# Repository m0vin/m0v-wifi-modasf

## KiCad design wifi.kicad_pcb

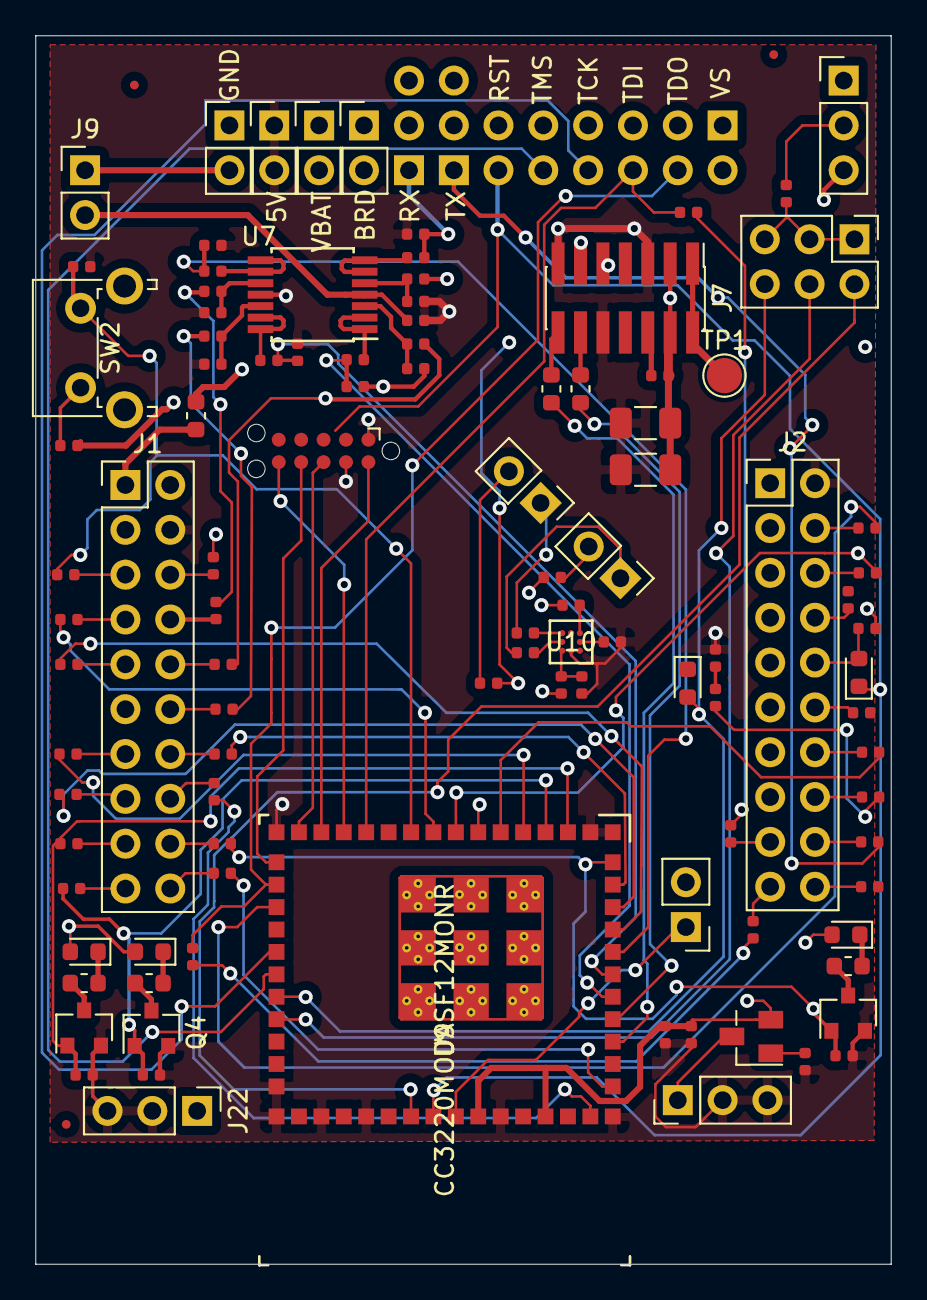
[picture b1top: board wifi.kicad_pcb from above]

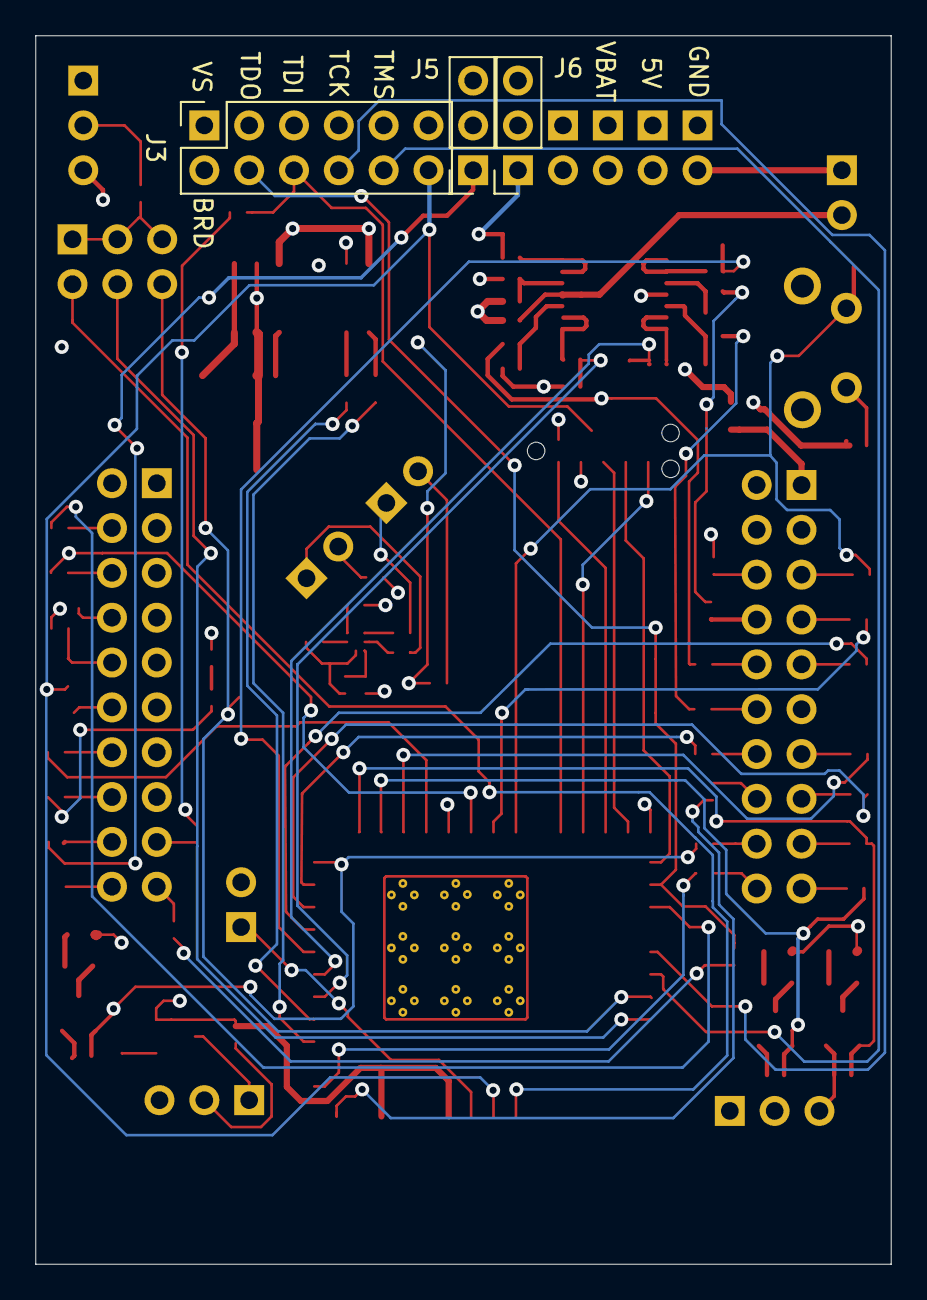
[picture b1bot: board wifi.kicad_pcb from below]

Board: 4 copper layers, 48.5 x 69.6 mm, 109 parts (3 on the bottom side), 107 nets.

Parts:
C26, C27, C28, C29, C30: 0.01uF; C_0402_1005Metric
C33, C34, C35: 0.1uF; C_0402_1005Metric
C41, C42: 100uF; C_1206_3216Metric
D4, D5: D_Schottky; D_0603_1608Metric
D8, D9, D10: LED; LED_0603_1608Metric
FID1, FID2, FID3: Fiducial; Fiducial_0.5mm_Mask1mm
J1, J2: Conn_02x10_Odd_Even; PinHeader_2x10_P2.54mm_Vertical
J3: Conn_02x06_Odd_Even; PinSocket_2x06_P2.54mm_Vertical
J5, J6: Conn_01x03; PinSocket_1x03_P2.54mm_Vertical
J7: Conn_02x07_Odd_Even; PinHeader_2x07_P1.27mm_Vertical_SMD
J9, J10, J14, J15, J16, J18, J19, J20: Conn_01x02; PinHeader_1x02_P2.54mm_Vertical
J12: Conn_02x03_Odd_Even; PinHeader_2x03_P2.54mm_Vertical
J13: Conn_02x05_Counter_Clockwise; Tag-Connect_TC2050-IDC-NL_2x05_P1.27mm_Vertical_CC_SMD
J21, J22, J26: Conn_01x03; PinHeader_1x03_P2.54mm_Vertical
Q4, Q6, Q7: BSS138; SOT-23
Q5: TP0610T; SuperSOT-3
R31, R136: 1K; R_0402_1005Metric
R33, R34: 33; R_0603_1608Metric
R38: 0; R_0603_1608Metric
R42, R44, R46, R49, R50, R52, R53, R54, R56, R57, R58, R60, R62, R63, R64, R65, R66, R67, R68, R69, R70, R71, R72, R73, R74, R104, R105, R114, R119, R121, R126, R127, R132, R133, R152: 0; R_0402_1005Metric
R84, R87, R92, R93: 470; R_0402_1005Metric
R85, R86, R94, R95: 576K; R_0402_1005Metric
R88, R89, R96, R97: 422K; R_0402_1005Metric
R107: 270; R_0402_1005Metric
R109: 2.2K; R_0402_1005Metric
R113, R139: 10K; R_0402_1005Metric
R134, R149, R150, R151: 100K; R_0402_1005Metric
R145, R146, R147: 270; R_0603_1608Metric
SW2: SW_DIP_x01; SW_Tactile_SPST_Angled_PTS645Vx31-2LFS
TP1: TestPoint; TestPoint_Pad_D2.0mm
U7: OPA4340UA; TSSOP-14_4.4x5mm_P0.65mm
U9: CC3220MODASF12MONR
U10: TMP006AIYZFR

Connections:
/ANA_IN1: R50.2, R86.2
/ANA_IN2: R58.2, R94.2
/ANA_IN3: R62.2, R95.2
/ANA_IN4: R54.2, R85.1
/CC_nRESET: D5.1, J3.12, J13.2, U9.35
/GPIO: J1.9, R57.1
/LP_GPIO_01: J5.1, R64.1
/LP_GPIO_02: C28.2, J6.1, R87.2
/LP_RESET_OUT: D5.2, J2.10, R134.2
/P01_GPIO_10: J7.9, Q6.1, R71.2, R121.2, R150.1, U9.3
/P02_GPIO_11: J7.11, Q4.1, R73.2, R127.2, R149.1, U9.4
/P03_GPIO_12: R53.2, U9.9
/P04_GPIO_13: R49.2, R139.1, SW2.2, U9.10
/P05_GPIO_14: R65.2, U9.5
/P06_GPIO_15: R56.1, U9.6
/P08_GPIO_17: R44.1, U9.8
/P16_GPIO_23: R63.2, R105.2
/P16_JTAG_TDI: J3.6, R105.1, U9.12
/P17_GPIO_24: R67.2, R104.2
/P17_JTAG_TDO: J3.4, R104.1, U9.18
/P18_GPIO_28: R42.1, U9.19
/P19_JTAG_TCK: J3.8, U9.21
/P20_JTAG_TMS: J3.10, U9.22
/P21_GPIO_25: R60.1, R109.1
/P50_GPIO_00: R74.2, U9.44
/P53_GPIO_30: R70.2, U9.42
/P55_GPIO_01: J5.2, R34.1, U9.46
/P57_GPIO_02: J6.2, R33.1, U9.47
/P58_GPIO_03: C29.2, R92.2, U9.48
/P59_GPIO_04: C30.2, R93.2, U9.49
/P60_GPIO_05: C27.2, R84.2, U9.50
/P61_GPIO_06: R57.2, U9.51
/P62_GPIO_07: R69.2, U9.52
/P63_GPIO_08: R66.2, U9.53
/P64_GPIO_09: Q7.1, R72.2, R151.1, U9.54
/PWR: J1.1, R38.1
/RX: J1.5, R49.1
/SENS_I2C_SCL: J14.1, R132.2
/SENS_I2C_SDA: J15.1, R133.1
/SOP0: J12.2, U9.34
/SOP1: J12.4, U9.24
/SOP2: D4.2, J12.6, U9.23
/SPI_CLK: J13.8, U9.15
/SPI_CS_IN: J13.10, U9.14
/SPI_MISO: J13.6, U9.13
/SPI_MOSI: J13.7, U9.17
/TX: J1.7, R53.1
/VBAT_CC: C33.1, C34.1, C41.2, C42.2, J7.3, J7.4, J10.2, J18.2, J26.3, Q5.2, R31.2, R38.2, U9.37, U9.40
/VCC_5V: J1.2, J19.2, J22.1
/VCC_BRD: D8.2, D9.2, D10.2, J3.2, J9.1, J16.2, J26.1, R114.1, R119.2, R134.1, R136.1
/VCC_LDO_3V3: J16.1, J18.1
/VCC_OPAMP: C26.2, J9.2, U7.4
GND: C26.1, C27.1, C28.1, C29.1, C30.1, C33.2, C34.2, C35.1, C41.1, C42.1, J1.4, J2.2, J7.5, J7.10, J7.13, J13.1, J13.9, J20.1, J20.2, J21.2, J21.3, J22.2, J22.3, Q4.2, Q6.2, Q7.2, R88.1, R89.1, R96.1, R97.1, R113.1, R126.1, R139.2, R149.2, R150.2, R151.2, R152.2, U7.11, U9.1, U9.2, U9.16, U9.27, U9.28, U9.30, U9.32, U9.38, U9.43, U9.55, U9.56, U9.57, U9.58, U9.59, U9.60, U9.61, U9.62, U9.63, U10.A1, U10.A2
unnamed: C35.2, R114.2, U10.A3
unnamed: D4.1, R109.2, R113.2
unnamed: D8.1, R146.1
unnamed: D9.1, R145.1
unnamed: D10.1, R147.1
unnamed: J1.6, R50.1
unnamed: J1.8, R54.1
unnamed: J1.10, R58.1
unnamed: J1.12, R62.1
unnamed: J1.13, R65.1
unnamed: J1.14, R66.1
unnamed: J1.15, R69.1
unnamed: J1.16, R70.1
unnamed: J1.17, R71.1
unnamed: J1.18, R72.1
unnamed: J1.19, R73.1
unnamed: J1.20, R74.1
unnamed: J2.4, R42.2
unnamed: J2.6, R44.2
unnamed: J2.8, R46.2
unnamed: J2.12, R52.2
unnamed: J2.14, R56.2
unnamed: J2.16, R60.2
unnamed: J2.17, R63.1
unnamed: J2.18, R64.2
unnamed: J2.19, R67.1
unnamed: J2.20, R68.2
unnamed: J7.1, J7.2, TP1.1
unnamed: J7.6, R31.1
unnamed: J7.12, R33.2
unnamed: J7.14, R34.2
unnamed: J10.1, U9.36
unnamed: J12.1, J12.3, J12.5, R107.1
unnamed: J14.2, R121.1
unnamed: J15.2, R127.1
unnamed: J21.1, Q5.3
unnamed: J26.2, R107.2
unnamed: Q4.3, R146.2
unnamed: Q5.1, R152.1
unnamed: Q6.3, R145.2
unnamed: Q7.3, R147.2
unnamed: R84.1, U7.8, U7.9
unnamed: R85.2, R88.2, U7.10
unnamed: R86.1, R89.2, U7.5
unnamed: R87.1, U7.6, U7.7
unnamed: R92.1, U7.1, U7.2
unnamed: R93.1, U7.13, U7.14
unnamed: R94.1, R96.2, U7.3
unnamed: R95.1, R97.2, U7.12
unnamed: R119.1, U10.C1
unnamed: R126.2, U10.B1
unnamed: R132.1, U10.B3
unnamed: R133.2, U10.C3
unnamed: R136.2, SW2.1

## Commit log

2019-11-13 Fixes for Aisler
2020-08-04 MODASF initial commit
2020-08-14 Updated BoM, decided to use 3 LEDs and switches from cc3220s layout
2020-08-28 Smaller board size, removed SW3

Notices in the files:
parts and their libraries:
Copyright 2016 Accelerated Designs. All rights reserved.
